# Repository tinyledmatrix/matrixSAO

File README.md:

# matrixSAO
tiny led matrix SAO

see also here:
https://hackaday.io/project/202620

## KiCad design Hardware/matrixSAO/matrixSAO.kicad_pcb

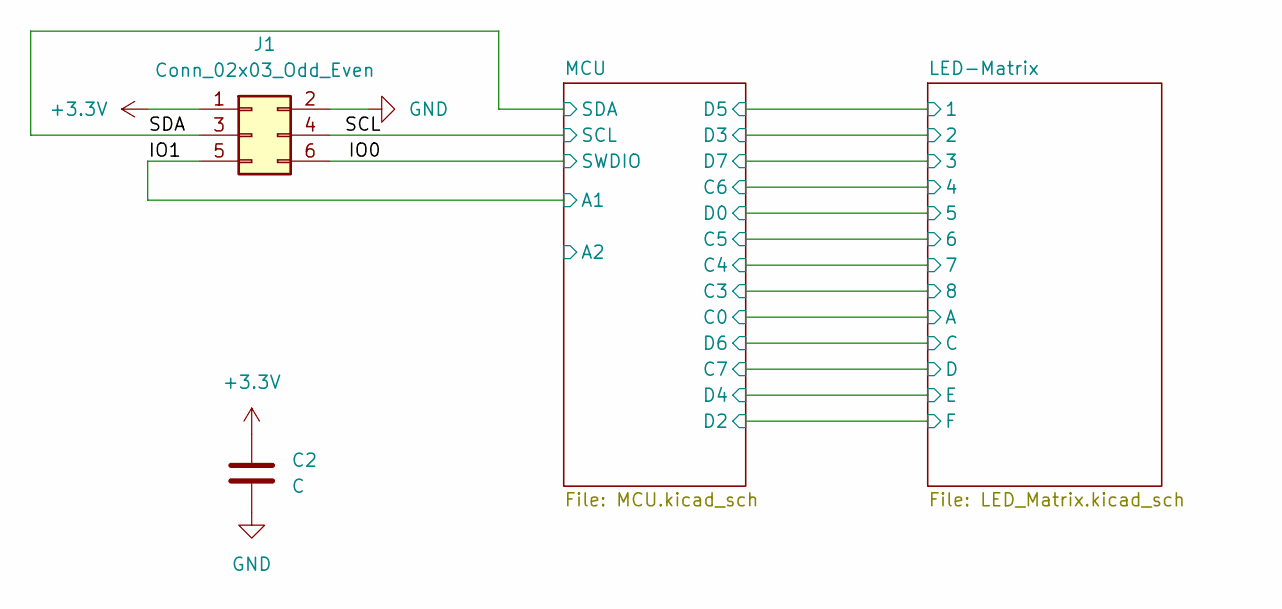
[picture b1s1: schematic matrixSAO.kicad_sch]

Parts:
C2: C; C_0402_min; LCSC C16772
J1: Conn_02x03_Odd_Even; IDC-Header_2x03_P2.54mm_Vertical; LCSC C4749192

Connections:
+3.3V: C2.2, J1.1; also elsewhere on the board
/IO0: J1.6; also elsewhere on the board
/IO1: J1.5; also elsewhere on the board
/SCL: J1.4; also elsewhere on the board
/SDA: J1.3; also elsewhere on the board
GND: C2.1, J1.2; also elsewhere on the board

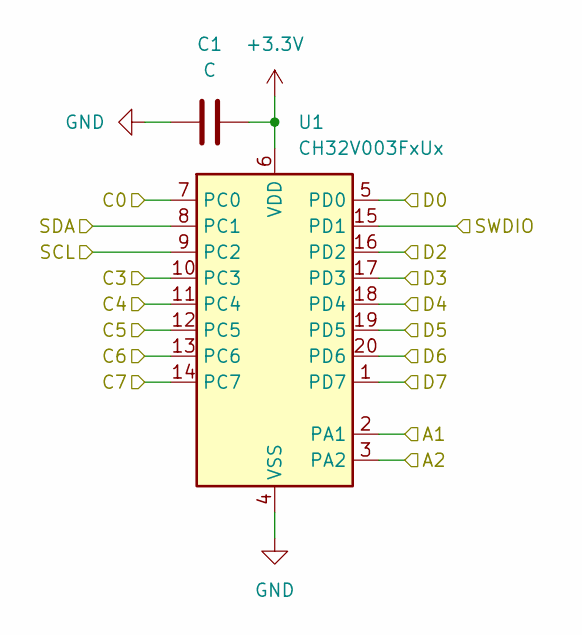
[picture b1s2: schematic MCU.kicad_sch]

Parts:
C1: C; C_0402_min; LCSC C16772
U1: CH32V003FxUx; QFN-20-1EP_3x3mm_P0.4mm_EP1.65x1.65mm; LCSC C5299908

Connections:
+3.3V: C1.2, U1.6 (VDD); also elsewhere on the board
/IO0: U1.15 (PD1); also elsewhere on the board
/IO1: U1.2 (PA1); also elsewhere on the board
/LED-Matrix/1: U1.19 (PD5); also elsewhere on the board
/LED-Matrix/2: U1.17 (PD3); also elsewhere on the board
/LED-Matrix/3: U1.1 (PD7); also elsewhere on the board
/LED-Matrix/4: U1.13 (PC6); also elsewhere on the board
/LED-Matrix/5: U1.5 (PD0); also elsewhere on the board
/LED-Matrix/6: U1.12 (PC5); also elsewhere on the board
/LED-Matrix/7: U1.11 (PC4); also elsewhere on the board
/LED-Matrix/8: U1.10 (PC3); also elsewhere on the board
/LED-Matrix/A: U1.7 (PC0); also elsewhere on the board
/LED-Matrix/C: U1.20 (PD6); also elsewhere on the board
/LED-Matrix/D: U1.14 (PC7); also elsewhere on the board
/LED-Matrix/E: U1.18 (PD4); also elsewhere on the board
/LED-Matrix/F: U1.16 (PD2); also elsewhere on the board
/MCU/A2: U1.3 (PA2)
/SCL: U1.9 (PC2); also elsewhere on the board
/SDA: U1.8 (PC1); also elsewhere on the board
GND: C1.1, U1.4 (VSS), U1.21 (VSS); also elsewhere on the board

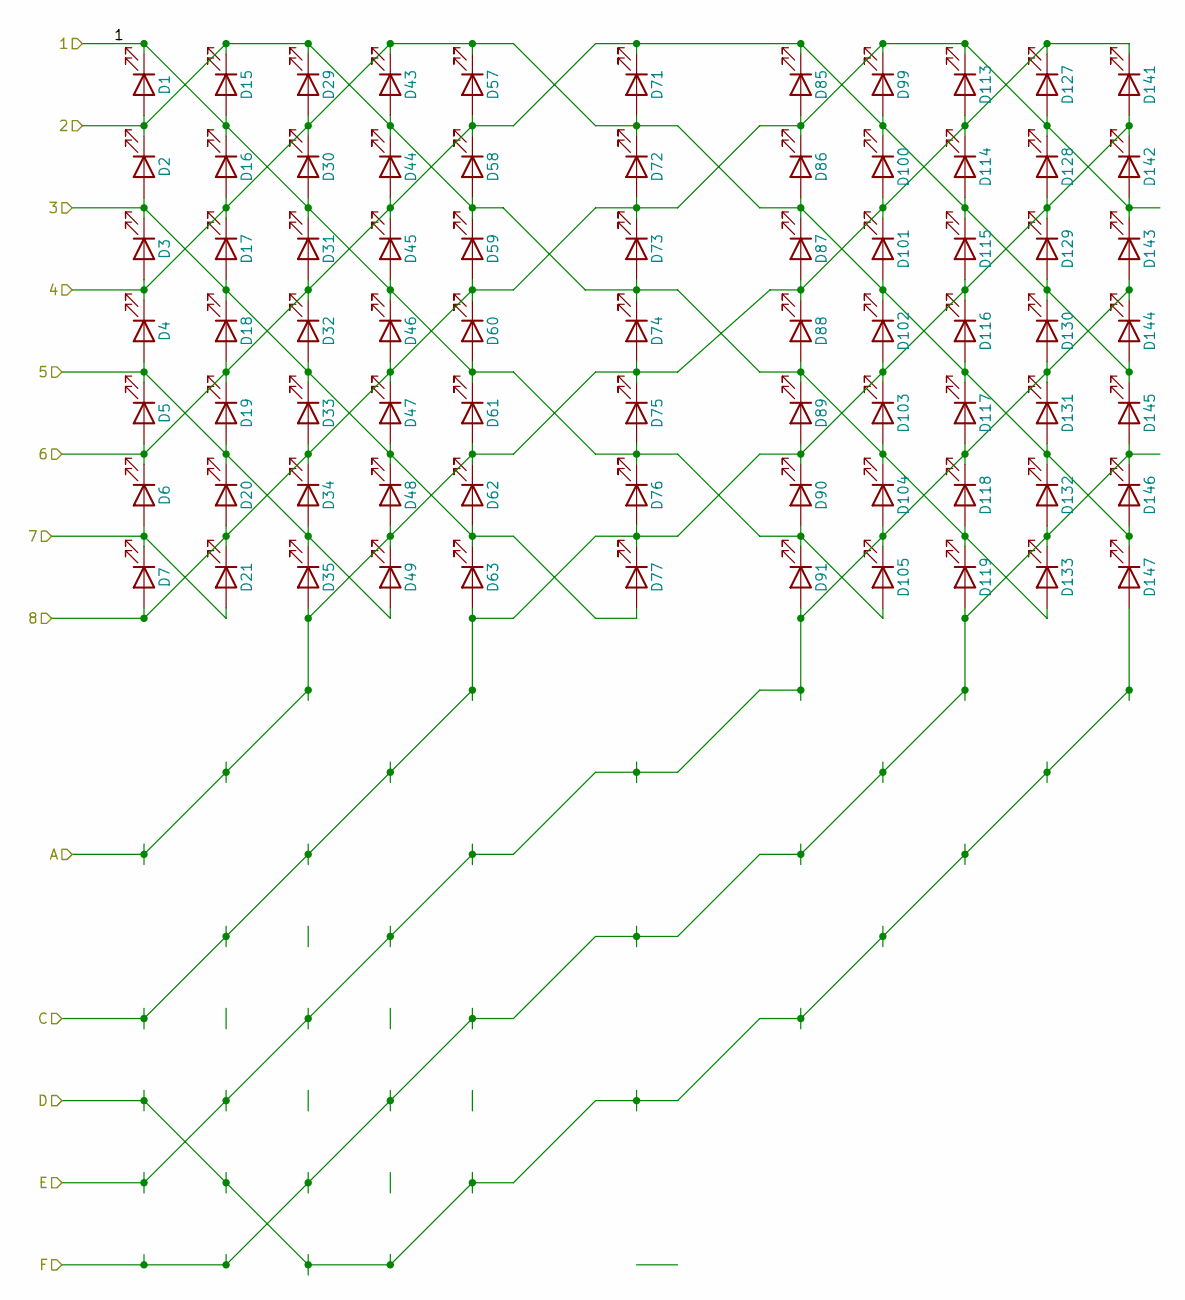
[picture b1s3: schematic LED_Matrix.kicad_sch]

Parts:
D1, D2, D3, D4, D5, D6, D7, D15, D16, D17, D18, D19, D20, D21, D29, D30, D31, D32, D33, D34, D35, D43, D44, D45, D46, D47, D48, D49, D57, D58, D59, D60, D61, D62, D63, D71, D72, D73, D74, D75, D76, D77, D85, D86, D87, D88, D89, D90, D91, D99, D100, D101, D102, D103, D104, D105, D113, D114, D115, D116, D117, D118, D119, D127, D128, D129, D130, D131, D132, D133, D141, D142, D143, D144, D145, D146, D147: LED; LCSC C965793

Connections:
/LED-Matrix/1: D1.1 (K), D15.2 (A), D16.1 (K), D30.2 (A), D31.1 (K), D45.2 (A), D46.1 (K), D60.2 (A), D61.1 (K), D75.2 (A), D76.1 (K), D90.2 (A), D91.1 (K), D105.2 (A); also elsewhere on the board
/LED-Matrix/2: D1.2 (A), D2.1 (K), D15.1 (K), D29.1 (K), D43.2 (A), D44.1 (K), D58.2 (A), D59.1 (K), D73.2 (A), D74.1 (K), D88.2 (A), D89.1 (K), D103.2 (A), D104.1 (K), D118.2 (A), D119.1 (K), D133.2 (A); also elsewhere on the board
/LED-Matrix/3: D2.2 (A), D3.1 (K), D17.2 (A), D18.1 (K), D32.2 (A), D33.1 (K), D47.2 (A), D48.1 (K), D62.2 (A), D63.1 (K), D77.2 (A); also elsewhere on the board
/LED-Matrix/4: D3.2 (A), D4.1 (K), D16.2 (A), D17.1 (K), D29.2 (A), D30.1 (K), D43.1 (K), D57.1 (K), D71.2 (A), D72.1 (K), D86.2 (A), D87.1 (K), D101.2 (A), D102.1 (K), D116.2 (A), D117.1 (K), D131.2 (A), D132.1 (K), D146.2 (A), D147.1 (K); also elsewhere on the board
/LED-Matrix/5: D4.2 (A), D5.1 (K), D19.2 (A), D20.1 (K), D34.2 (A), D35.1 (K), D49.2 (A); also elsewhere on the board
/LED-Matrix/6: D5.2 (A), D6.1 (K), D18.2 (A), D19.1 (K), D31.2 (A), D32.1 (K), D44.2 (A), D45.1 (K), D57.2 (A), D58.1 (K), D71.1 (K), D85.1 (K), D99.2 (A), D100.1 (K), D114.2 (A), D115.1 (K), D129.2 (A), D130.1 (K), D144.2 (A), D145.1 (K); also elsewhere on the board
/LED-Matrix/7: D6.2 (A), D7.1 (K), D21.2 (A); also elsewhere on the board
/LED-Matrix/8: D7.2 (A), D20.2 (A), D21.1 (K), D33.2 (A), D34.1 (K), D46.2 (A), D47.1 (K), D59.2 (A), D60.1 (K), D72.2 (A), D73.1 (K), D85.2 (A), D86.1 (K), D99.1 (K), D113.1 (K), D127.2 (A), D128.1 (K), D142.2 (A), D143.1 (K); also elsewhere on the board
/LED-Matrix/A: D35.2 (A), D48.2 (A), D49.1 (K), D61.2 (A), D62.1 (K), D74.2 (A), D75.1 (K), D87.2 (A), D88.1 (K), D100.2 (A), D101.1 (K), D113.2 (A), D114.1 (K), D127.1 (K), D141.1 (K); also elsewhere on the board
/LED-Matrix/C: D63.2 (A), D76.2 (A), D77.1 (K), D89.2 (A), D90.1 (K), D102.2 (A), D103.1 (K), D115.2 (A), D116.1 (K), D128.2 (A), D129.1 (K), D141.2 (A), D142.1 (K); also elsewhere on the board
/LED-Matrix/D: D147.2 (A); also elsewhere on the board
/LED-Matrix/E: D91.2 (A), D104.2 (A), D105.1 (K), D117.2 (A), D118.1 (K), D130.2 (A), D131.1 (K), D143.2 (A), D144.1 (K); also elsewhere on the board
/LED-Matrix/F: D119.2 (A), D132.2 (A), D133.1 (K), D145.2 (A), D146.1 (K); also elsewhere on the board

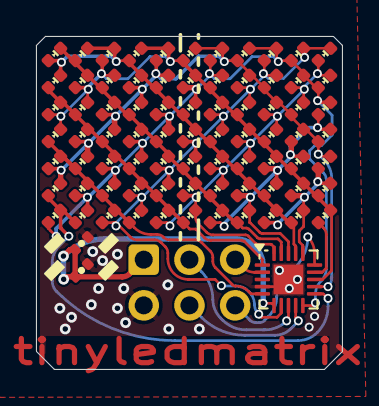
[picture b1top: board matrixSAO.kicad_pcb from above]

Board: 2 copper layers, 17.0 x 18.5 mm, 81 parts (1 on the bottom side), 19 nets.

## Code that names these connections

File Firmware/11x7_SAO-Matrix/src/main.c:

#include "ch32fun.h"
#include <stdio.h>
#include "font5x7.h"
//#include <ch32v00x_conf.h> 
#include "flash.h"

#define COL_COUNT 11
#define ROW_COUNT 7
#define BUFFER_COL_COUNT (27*6)   //30*8=180

#define ANODE_PIN 0
#define CATHODE_PIN 1

#define LPin1 PD5
#define LPin2 PD3
#define LPin3 PD7
#define LPin4 PC6
#define LPin5 PD0
#define LPin6 PC5
#define LPin7 PC4

#define LPinB PC3
#define LPinA PC0
#define LPinC PD6
#define LPinD PC7
#define LPinE PD4
#define LPinF PD2

static const uint8_t LED_MATRIX [ROW_COUNT][COL_COUNT][2]=     // row, col, LED-anode, LED-cathode - this maps the LEDs to the Matrix 
{
//    1               2               3               4               5               6               7               8               9               10              11
    { {LPin2, LPin1}, {LPin1, LPin2}, {LPin4, LPin2}, {LPin2, LPin4}, {LPin6, LPin4}, {LPin4, LPin6}, {LPinB, LPin6}, {LPin6, LPinB}, {LPinA, LPinB}, {LPinB, LPinA}, {LPinC, LPinA} },
    { {LPin3, LPin2}, {LPin4, LPin1}, {LPin1, LPin4}, {LPin6, LPin2}, {LPin2, LPin6}, {LPinB, LPin4}, {LPin4, LPinB}, {LPinA, LPin6}, {LPin6, LPinA}, {LPinC, LPinB}, {LPinB, LPinC} } ,
    { {LPin4, LPin3}, {LPin3, LPin4}, {LPin6, LPin1}, {LPin1, LPin6}, {LPinB, LPin2}, {LPin2, LPinB}, {LPinA, LPin4}, {LPin4, LPinA}, {LPinC, LPin6}, {LPin6, LPinC}, {LPinE, LPinB} },	
    { {LPin5, LPin4}, {LPin6, LPin3}, {LPin3, LPin6}, {LPinB, LPin1}, {LPin1, LPinB}, {LPinA, LPin2}, {LPin2, LPinA}, {LPinC, LPin4}, {LPin4, LPinC}, {LPinE, LPin6}, {LPin6, LPinE} },	
    { {LPin6, LPin5}, {LPin5, LPin6}, {LPinB, LPin3}, {LPin3, LPinB}, {LPinA, LPin1}, {LPin1, LPinA}, {LPinC, LPin2}, {LPin2, LPinC}, {LPinE, LPin4}, {LPin4, LPinE}, {LPinF, LPin6} },	
    { {LPin7, LPin6}, {LPinB, LPin5}, {LPin5, LPinB}, {LPinA, LPin3}, {LPin3, LPinA}, {LPinC, LPin1}, {LPin1, LPinC}, {LPinE, LPin2}, {LPin2, LPinE}, {LPinF, LPin4}, {LPin4, LPinF} },	
    { {LPinB, LPin7}, {LPin7, LPinB}, {LPinA, LPin5}, {LPin5, LPinA}, {LPinC, LPin3}, {LPin3, LPinC}, {LPinE, LPin1}, {LPin1, LPinE}, {LPinF, LPin2}, {LPin2, LPinF}, {LPinD, LPin4} }
};

volatile uint8_t MatrixBuffer[ROW_COUNT][BUFFER_COL_COUNT];      // yes one byte per LED - for future Dimming or so 

static uint8_t activeCol = 0;
static uint8_t activeRow = 0;
static uint8_t oldCol    = 0;
static uint8_t oldRow    = 0;
static uint8_t bufferOffset =0;

void doMatrixStuff(void)
{
    oldCol=activeCol;
    oldRow=activeRow;
    
    activeCol++;                                // next Col
    if (activeCol>(COL_COUNT-1)) activeCol=0;

    activeRow++;                                // next Row 
    if (activeRow>(ROW_COUNT-1)) activeRow=0;

    //reset last LED
    funPinMode( LED_MATRIX[oldRow][oldCol][ANODE_PIN],   GPIO_Speed_10MHz | GPIO_CNF_IN_PUPD ); 
    funPinMode( LED_MATRIX[oldRow][oldCol][CATHODE_PIN], GPIO_Speed_10MHz | GPIO_CNF_IN_PUPD ); 
    Delay_Us(10);

    //set new LED
    if ((MatrixBuffer[activeRow][activeCol+bufferOffset])>0)
    {
        funPinMode( LED_MATRIX[activeRow][activeCol][ANODE_PIN],   GPIO_Speed_10MHz | GPIO_CNF_OUT_PP ); 
        funDigitalWrite( LED_MATRIX[activeRow][activeCol][ANODE_PIN], FUN_HIGH );

        funPinMode( LED_MATRIX[activeRow][activeCol][CATHODE_PIN],   GPIO_Speed_10MHz | GPIO_CNF_OUT_PP ); 
        funDigitalWrite( LED_MATRIX[activeRow][activeCol][CATHODE_PIN], FUN_LOW);
    }
}

void initMatrixBufferWithDummyData(void)
{
    uint8_t alternater=1;
    uint8_t row=0;
    uint8_t col=0;

    while (row<ROW_COUNT)
    {
        while(col<COL_COUNT)
        {
            MatrixBuffer[row][col]=(alternater++)&1;    //this should activate every secon LED and create a checkerboard pattern on a 11 collum mA trix  
            col++;
        }
        col=0;
        row++;
    }
}

void putASCIIatPos(char index, uint16_t pos)
{
    uint8_t colCounter =0;
    if ((pos+5)>BUFFER_COL_COUNT)  return;   // don't allow clipped Letters for now  
	if ((index-=32)>96)     return;   // if ascii>127
        	
    while (colCounter<5)
    {
        for(uint8_t i=0; i<ROW_COUNT; i++)
        {
            if ( (uint8_t)Font5x7[index][colCounter] & (1<<i) )
                MatrixBuffer[i][pos+colCounter]=0xFF;
        }
        colCounter++;
    }
}

void putStringToBuffer(char* inString)
{
    uint16_t i=0;
    while ( (inString[i]!='/0') && (i<BUFFER_COL_COUNT/6) )
    {
        putASCIIatPos(inString[i], i*6);
        i++;
    }
}

uint16_t counter=1;
uint16_t t=1;



int main (void)
{
   //FLASH_Unlock();
   // FLASH_EraseOptionBytes();
   // FLASH_UserOptionByteConfig(OB_STOP_NoRST, OB_STDBY_NoRST, OB_RST_NoEN, OB_PowerON_Start_Mode_USER);
   // FLASH_Unlock();
    //unlockD7();
    SystemInit();
    //unlockD7();
    Delay_Ms(100);
    funGpioInitAll();

/*
    FLASH_Unlock();
    FLASH_EraseOptionBytes();
    FLASH_UserOptionByteConfig(OB_STOP_NoRST, OB_STDBY_NoRST, OB_RST_NoEN, OB_PowerON_Start_Mode_USER);
    FLASH_Unlock();*/

    //Init IOs
    funPinMode( PC0, GPIO_Speed_10MHz | GPIO_CNF_IN_PUPD );     // on port C 
    funPinMode( PC3, GPIO_Speed_10MHz | GPIO_CNF_IN_PUPD );
    funPinMode( PC4, GPIO_Speed_10MHz | GPIO_CNF_IN_PUPD );
    funPinMode( PC5, GPIO_Speed_10MHz | GPIO_CNF_IN_PUPD );
    funPinMode( PC6, GPIO_Speed_10MHz | GPIO_CNF_IN_PUPD );
    funPinMode( PC7, GPIO_Speed_10MHz | GPIO_CNF_IN_PUPD );

    funPinMode( PD0, GPIO_Speed_10MHz | GPIO_CNF_IN_PUPD );     // on port D
    funPinMode( PD2, GPIO_Speed_10MHz | GPIO_CNF_IN_PUPD ); 
    funPinMode( PD3, GPIO_Speed_10MHz | GPIO_CNF_IN_PUPD ); 
    funPinMode( PD4, GPIO_Speed_10MHz | GPIO_CNF_IN_PUPD ); 
    funPinMode( PD5, GPIO_Speed_10MHz | GPIO_CNF_IN_PUPD ); 
    funPinMode( PD6, GPIO_Speed_10MHz | GPIO_CNF_IN_PUPD ); 
    funPinMode( PD7, GPIO_Speed_10MHz | GPIO_CNF_IN_PUPD ); 

    //funDigitalWrite(PD7, FUN_LOW);

    //initMatrixBufferWithDummyData();
    //MatrixBuffer[1][2]=1;
    //MatrixBuffer[3][3]=1;
    
    //putASCIIatPos('T',1);
    /*
    putASCIIatPos(' ',0);
    putASCIIatPos(' ',6);
    putASCIIatPos('H',11);
    putASCIIatPos('e',11+6);
    putASCIIatPos('l',11+6*2);
    putASCIIatPos('l',11+6*3);
    putASCIIatPos('o',11+6*4);
    putASCIIatPos(' ',11+6*5);
    putASCIIatPos('f',11+6*6);
    putASCIIatPos('r',11+6*7);
    putASCIIatPos('o',11+6*8);
    putASCIIatPos('m',11+6*9);
    putASCIIatPos(' ',11+6*10);
    putASCIIatPos('@',11+6*11);
    putASCIIatPos('t',11+6*12);
    putASCIIatPos('i',11+6*13);
    putASCIIatPos('n',11+6*14);
    putASCIIatPos('y',11+6*15);
    putASCIIatPos('l',11+6*16);
    putASCIIatPos('e',11+6*17);
    putASCIIatPos('d',11+6*18);
    putASCIIatPos('m',11+6*19);
    putASCIIatPos('a',11+6*20);
    putASCIIatPos('t',11+6*21);
    putASCIIatPos('r',11+6*22);
    putASCIIatPos('i',11+6*23);
    putASCIIatPos('x',11+6*24);
    putASCIIatPos(' ',11+6*25);
    putASCIIatPos(' ',11+6*26); //167
    */
    putStringToBuffer("  Hello from @tinyledmatrix");

    bufferOffset=0;

    //while(counter)


    while(1)
    {
        doMatrixStuff();
        counter++;
        if (counter==4000)
        {
            counter=0;
            bufferOffset++;
            if (bufferOffset>BUFFER_COL_COUNT-5) bufferOffset=0;
        }
            
        //Delay_Us(100);
        
    }
}   

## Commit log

2025-02-12 kicad
2025-02-16 ongoign work Schematic
2025-02-17 some work
2025-02-26 Order at JLCPPCB
2025-03-15 cleaned Schematic
2025-03-15 Added Firmware
2025-03-17 fix e/d problem
    two letters were printed over each other, this fixes it.
2025-06-21 some work/tests on code
2025-06-21 Added a string Function
